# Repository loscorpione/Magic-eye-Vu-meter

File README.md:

# Magic-eye-Vu-meter
VU-meter with magic eye VT138

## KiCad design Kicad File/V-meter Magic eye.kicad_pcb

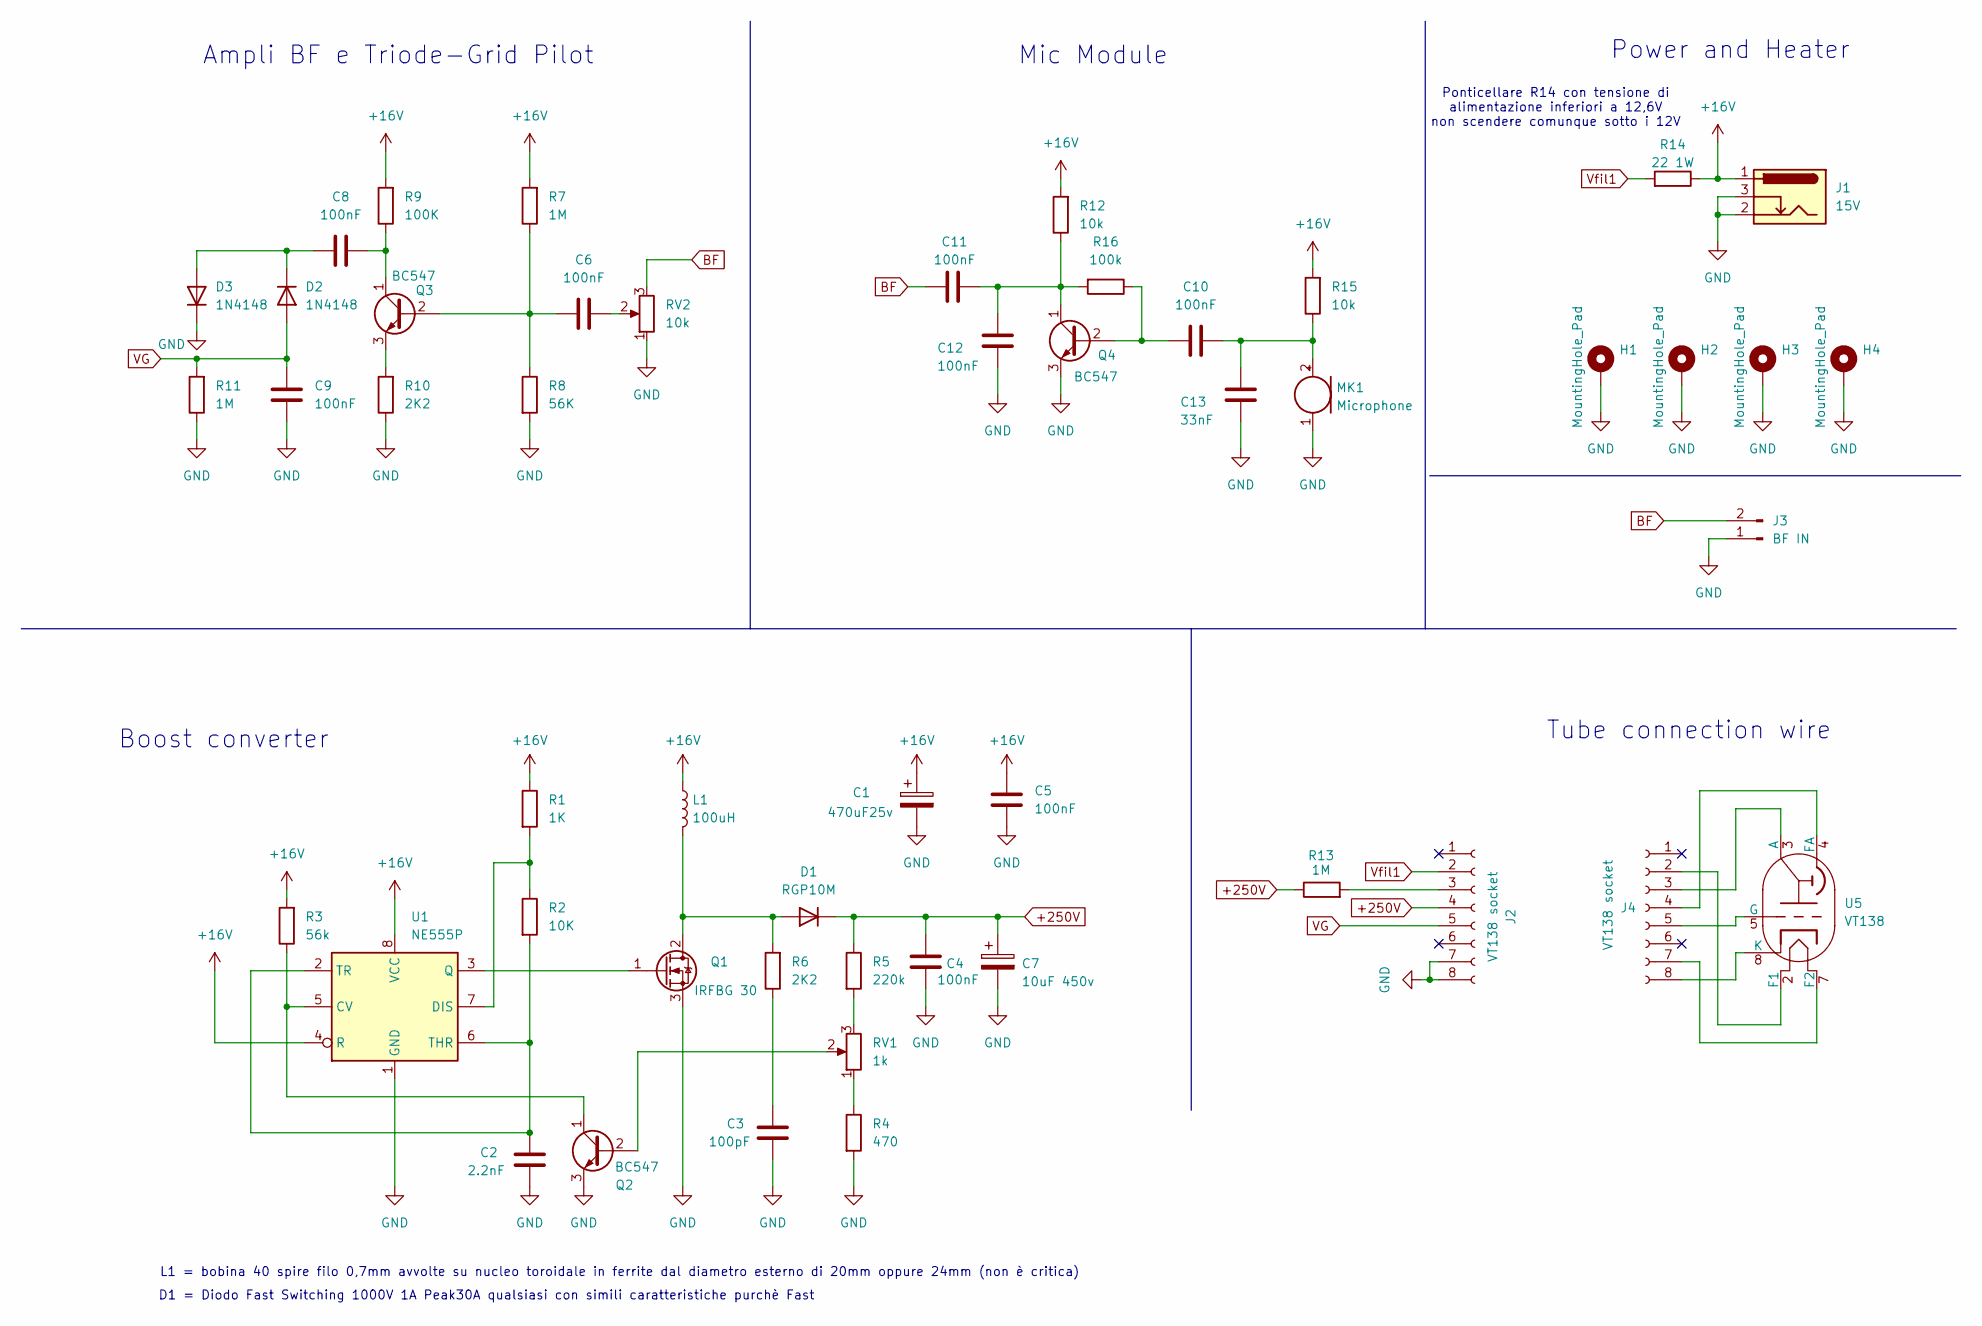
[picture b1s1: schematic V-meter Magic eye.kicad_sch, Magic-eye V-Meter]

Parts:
C1: 470uF25v; CP_Radial_D10.0mm_P5.00mm
C2: 2.2nF; C_Rect_L7.0mm_W2.5mm_P5.00mm
C3: 100pF; C_Disc_D7.5mm_W4.4mm_P5.00mm
C4, C5, C6, C8, C9, C10, C11, C12: 100nF; C_Rect_L7.0mm_W2.5mm_P5.00mm
C7: 10uF 450v; CP_Radial_D10.0mm_P5.00mm
C13: 33nF; C_Rect_L7.0mm_W2.5mm_P5.00mm
D1: RGP10M; D_DO-41_SOD81_P10.16mm_Horizontal
D2, D3: 1N4148; D_DO-35_SOD27_P7.62mm_Horizontal
H1, H2, H3, H4: MountingHole_Pad; MountingHole_3.2mm_M3_DIN965_Pad
J1: 15V; BarrelJack_Horizontal
J2, J4: VT138 socket; TE_826576-8_1x08_P3.96mm_Vertical
J3: BF IN; PinHeader_1x02_P2.54mm_Vertical
L1: 100uH; L_Toroid_Horizontal_D16.8mm_P14.70mm_Vishay_TJ3_BigPads
MK1: Microphone; POM-2244P-C3310-2-R
Q1: IRFBG 30; TO-220-3_Vertical
Q2, Q3, Q4: BC547; TO-92_Inline_Wide
R1: 1K; R_Axial_DIN0207_L6.3mm_D2.5mm_P10.16mm_Horizontal
R2: 10K; R_Axial_DIN0207_L6.3mm_D2.5mm_P10.16mm_Horizontal
R3: 56k; R_Axial_DIN0207_L6.3mm_D2.5mm_P10.16mm_Horizontal
R4: 470; R_Axial_DIN0207_L6.3mm_D2.5mm_P10.16mm_Horizontal
R5: 220k; R_Axial_DIN0207_L6.3mm_D2.5mm_P10.16mm_Horizontal
R6, R10: 2K2; R_Axial_DIN0207_L6.3mm_D2.5mm_P10.16mm_Horizontal
R7, R11, R13: 1M; R_Axial_DIN0207_L6.3mm_D2.5mm_P10.16mm_Horizontal
R8: 56K; R_Axial_DIN0207_L6.3mm_D2.5mm_P10.16mm_Horizontal
R9: 100K; R_Axial_DIN0207_L6.3mm_D2.5mm_P10.16mm_Horizontal
R12, R15: 10k; R_Axial_DIN0207_L6.3mm_D2.5mm_P10.16mm_Horizontal
R14: 22 1W; R_Axial_DIN0414_L11.9mm_D4.5mm_P15.24mm_Horizontal
R16: 100k; R_Axial_DIN0207_L6.3mm_D2.5mm_P10.16mm_Horizontal
RV1: 1k; Potentiometer_Vishay_T73XX_Horizontal
RV2: 10k; Potentiometer_Vishay_T73XX_Horizontal
U1: NE555P; DIP-8_W7.62mm
U5: VT138; Valve_Noval_P

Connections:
+16V: C1.1, C5.1, J1.1, L1.1, R1.1, R3.2, R7.2, R9.2, R12.2, R14.1, R15.2, U1.4 (R), U1.8 (VCC)
+250V: C4.1, C7.1, D1.1 (K), J2.4, R5.1, R13.1
BF: C11.1, J3.2, RV2.3
GND: C1.2, C2.2, C3.2, C4.2, C5.2, C7.2, C9.1, C12.1, C13.1, D3.1 (K), H1.1, H2.1, H3.1, H4.1, J1.2, J1.3, J2.7, J2.8, J3.1, MK1.1 (-), Q1.3 (S), Q2.3 (E), Q4.3 (E), R4.2, R8.2, R10.1, R11.1, RV2.1, U1.1 (GND)
unnamed: C3.1, R6.1
unnamed: C6.2, RV2.2
unnamed: D1.2 (A), L1.2, Q1.2 (D), R6.2
unnamed: C8.1, D2.1 (K), D3.2 (A)
unnamed: J2.3, R13.2
unnamed: J4.2, U5.2 (F1)
unnamed: J4.3, U5.3 (A)
unnamed: J4.4, U5.4 (FA)
unnamed: J4.5, U5.5 (G)
unnamed: J4.7, U5.7 (F2)
unnamed: J4.8, U5.8 (K)
unnamed: C10.2, C13.2, MK1.2 (+), R15.1
unnamed: Q1.1 (G), U1.3 (Q)
unnamed: Q2.2 (B), RV1.2
unnamed: Q2.1 (C), R3.1, U1.5 (CV)
unnamed: C6.1, Q3.2 (B), R7.1, R8.1
unnamed: C8.2, Q3.1 (C), R9.1
unnamed: Q3.3 (E), R10.2
unnamed: C10.1, Q4.2 (B), R16.1
unnamed: C11.2, C12.2, Q4.1 (C), R12.1, R16.2
unnamed: R4.1, RV1.1
unnamed: R5.2, RV1.3
unnamed: R1.2, R2.1, U1.7 (DIS)
unnamed: C2.1, R2.2, U1.2 (TR), U1.6 (THR)
VG: C9.2, D2.2 (A), J2.5, R11.2
Vfil1: J2.2, R14.2

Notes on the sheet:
Boost converter
Power and Heater
D1 = Diodo Fast Switching 1000V 1A Peak30A qualsiasi con simili caratteristiche purchè Fast
Mic Module
Tube connection wire
L1 = bobina 40 spire filo 0,7mm avvolte su nucleo toroidale in ferrite dal diametro esterno di 20mm oppure 24mm (non è critica)
Ponticellare R14 con tensione di alimentazione inferiori a 12,6V non scendere comunque sotto i 12V
Ampli BF e Triode-Grid Pilot

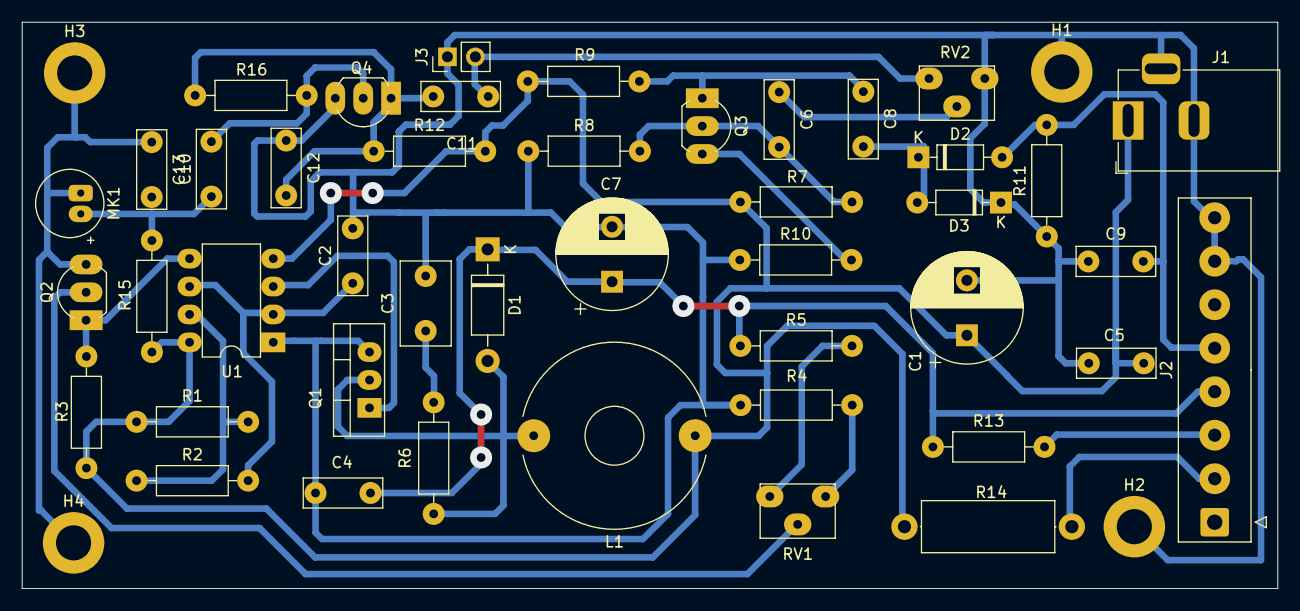
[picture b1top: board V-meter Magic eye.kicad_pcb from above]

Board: 2 copper layers, 114.3 x 51.6 mm, 48 parts (0 on the bottom side), 24 nets.

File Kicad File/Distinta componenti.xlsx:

Riferimento | Valore | Qty
C1 | 470uF25v | 1
C2 | 2.2nF | 1
C3 | 100pF | 1
C4,C5,C6,C8,C9,C10,C11,C12 | 100nF | 8
C7 | 10uF 450v | 1
C13 | 33nF | 1
D1 | RGP10M | 1
D2,D3 | 1N4148 | 2
J1 | Dc connector | 1
J3 | BF IN | 1
L1 | 100uH | 1
MK1 | Microphone | 1
Q1 | IRFBG 30 | 1
Q2,Q3,Q4 | BC547 | 3
R1 | 1K | 1
R2 | 10K | 1
R3 | 56k | 1
R4 | 470 | 1
R5 | 220k | 1
R6,R10 | 2K2 | 2
R7,R11,R13 | 1M | 3
R8 | 56K | 1
R9 | 100K | 1
R12,R15,RV2 | 10k | 3
R14 | 22 1W | 1
R16 | 100k | 1
RV1 | 1k | 1
U1 | NE555P | 1
U5 | VT138 | 1

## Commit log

2025-01-07 V 1.0
2025-01-11 V 1.1
    Inserito pdf dello schema elettrico PCB e montaggio componenti
2025-01-11 V 1.2
    Aggiunto distinta componenti
2025-01-12 V1.3
    inserito capacità riuzione rumore alimentazione
2025-03-10 aggiornamenti
